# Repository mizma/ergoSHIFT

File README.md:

ergoSHIFT arcade controller
========================================================================

_**Low profile 11 button leverless arcade controller with Acrylic shell**_

This repository contains Acrylic cut design files, PCB design files and code needed to make
an arcade controller that look like this:

Also, you can create custom artwork using the stencil provided in each hardware revision folder.

(*) Above sample Artwork based on an In-Game Screenshot + Official Fan-kit (©Cygames & ARK SYSTEM WORKS)

This controller is designed with the following concept:

* Create a reasonably compact and thin leverless arcade controller
* Layout 11 main buttons + 4 directional buttons to work with the latest
  Capcom Pro-Tour rule-set
* Shift the home position for the main button one column to the right to better utilize the
  more dextrous thumb and index finger instead of the little finger.
* Add the three additionally allowed buttons
* Make the button size compatible with Snackbox MICRO from [Junkfood Arcades](https://junkfoodarcades.com/)
    * I could not find good Injection molded options other than this one.
* Make the design reversible for southpaw use.
    * To assemble for left hand use, implement all buttons on the other side.
    * Controller Circuit (Pro Micro or RP2040) must be implemented on the same side
    * to compensate for the Controller Cicuitry being implemented in reverse, Acrylic layers will need to be
      stacked in a different order and thickness.  Refer to each revision README for details

Resulting button mappings will look like this:

There are currently two revisions of the ergoSHIFT.  It uses Kailh low profile (choc v1)
mechanical keyboard switches.  The table below lists their main features.
See the README for each version for details on how to make them.

version                                 | [rev1](./hardware-rev1/)            | [rev2](./hardware-rev2/)              | [rgb](./hardware-rgb/)                |
--------------------------------------- | ----------------------------------- | ------------------------------------- | ------------------------------------- |
Status                                  | Verified                            | Verified                              | Verified                              |
case dimensions                         | 233.17x147.67x14.6mm (excl. feet)   | 233.17x147.67x14.6mm (excl. feet)     | 233.17x147.67x14.6mm (excl. feet)     |
compatibility (using provided firmware) | PC, PS3, Xinput, Switch             | PC, PS3, PS4*, PS5*, Xinput, Switch   | PC, PS3, PS4*, PS5*, Xinput, Switch   |
add-on board                            | Sparkfun Qwiic Pro Micro            | SSD1306, SH1106 or SH1107 128x64 oled | SSD1306, SH1106 or SH1107 128x64 oled |
onboard chip                            | -                                   | RP2040                                | RP2040                                |
port                                    | USB-C                               | USB-C                                 | USB-C                                 |
SMT assembly required                   | no                                  | yes                                   | yes                                   |
OLED Support                            | no                                  | yes                                   | yes                                   |
RGB Support                             | no                                  | no                                    | yes                                   |
South-paw support                       | yes                                 | yes                                   | no                                    |
firmware                                | [ATmega32U4](firmwares_atmega32u4)  | [GP2040-CE](https://gp2040-ce.info/)**| [GP2040-CE](https://gp2040-ce.info/)**|

*) for details, see the documentation in the [GP2040-CE Console Compatibility FAQ](https://gp2040-ce.info/faq/faq-console-compatibility/)

**) See [GP2040 firmware page](./firmware_GP2040-CE/) for firmware with ergoSHIFT specific config.

LICENSE
------------------------------------------------------------------------

ergoSHIFT (c) by mizma

ergoSHIFT is licensed under a
Creative Commons Attribution-ShareAlike 4.0 International License.

You should have received a copy of the license along with this
work. If not, see <https://creativecommons.org/licenses/by-sa/4.0/>.

Some portions of the work uses derivative works of other libraries and or implementations.
Firmware and hardware designs are separately licensed depending on the licensing terms of
the works it uses.  Refer to the LICENSE files or README for the relevant terms for each
component.

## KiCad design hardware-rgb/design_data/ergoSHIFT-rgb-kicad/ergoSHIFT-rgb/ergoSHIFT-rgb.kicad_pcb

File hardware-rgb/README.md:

ergoSHIFT rev RGB
========================================================================

This is a RGB rev of the ergoSHIFT.  In this version, RGB LEDs were added to each Kailh button and can be assembled onto the board by JLCPCB (or another fab house), similar to the other SMT parts. 

The firmware from the [Original GP2040-CE website](https://gp2040-ce.info/downloads) will work along with enabling the RGB LED via the GP2040-CE Web Configurator.
You may also use the firmware in the [Firmware Directory](../firmware_GP2040-CE/) which support original OLED display layout.

This version of Ergoshift has been modified to only work in the standard (non Southpaw) configuration so that there is PCB area for RGB LEDs. The Kailh sockets are also required for this version (rev2 can use Kailh sockets or switches directly) and can only be installed in the normal configuration.

All other assembly steps are the same as the hardware-rev2 steps

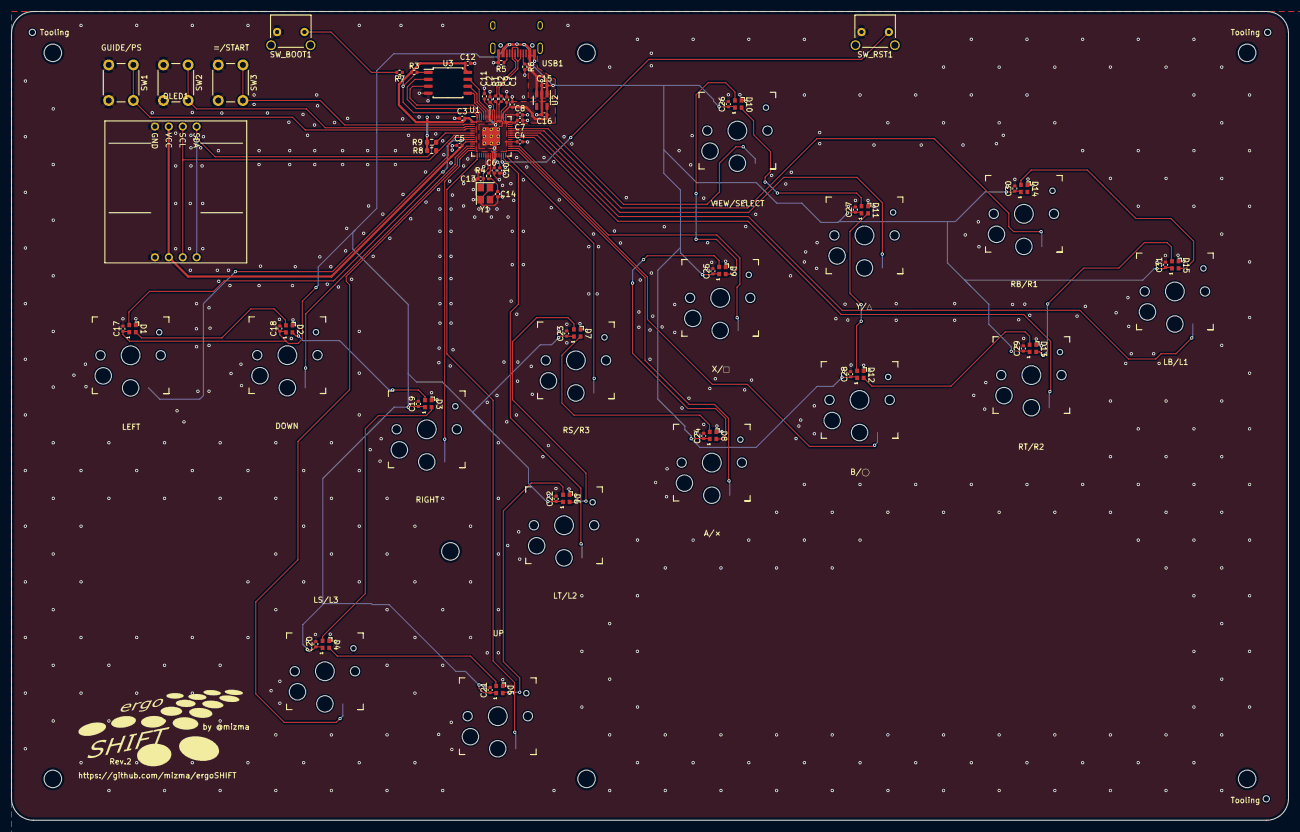
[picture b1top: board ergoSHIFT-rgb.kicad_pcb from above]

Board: 2 copper layers, 233.2 x 147.7 mm, 84 parts (0 on the bottom side), 56 nets.

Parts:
C1, C9, C15, C16: 1u; C_0402_1005Metric
C2, C3, C4, C5, C6, C7, C8, C10, C11, C12: 100n; C_0402_1005Metric
C13, C14: 30p; C_0402_1005Metric
C17, C18, C19, C20, C21, C22, C23, C24, C25, C26, C27, C28, C29, C30, C31: 100nF; C_0402_1005Metric
D1, D2, D3, D4, D5, D6, D7, D8, D9, D10, D11, D12, D13, D14, D15: SK6812-EC20; LED_SK6812_EC20_2.0x2.0mm
OLED1: OLED_DISP_0.96inch_Reversible
R1, R2: 27; R_0402_1005Metric
R3: 10k; R_0402_1005Metric
R4, R7: 1k; R_0402_1005Metric
R5, R6: 5.1k; R_0402_1005Metric
R8, R9: 4.7k; R_0603_1608Metric
SW1, SW2, SW3: SW_Push; SW_PUSH_6mm_H8.5mm
SW4, SW5, SW6, SW7, SW8, SW9, SW10, SW11, SW12, SW13, SW14, SW15, SW16, SW17, SW18: SW_Push; Kailh_socket_PG1350
SW_BOOT1: SW_PUSH; SW_Tactile_Yushakobo 3x6x4.3mm
SW_RST1: SW_PUSH; SW_Tactile_Yushakobo 3x6x4.3mm
Tooling: JLCPCB_Tooling
Tooling#2, Tooling#3: JLCPCB_Tooling
U1: RP2040; RP2040-QFN-56
U2: TLV73333PDBV; SOT-23-5
U3: W25Q128JVS; SOIC-8_5.23x5.23mm_P1.27mm
USB1: HRO-TYPE-C-31-M-12; HRO-TYPE-C-31-M-12-Assembly
Y1: Crystal_GND24; Crystal_SMD_3225-4Pin_3.2x2.5mm

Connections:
+1V1: C9.1, C10.1, C11.1, U1.23 (DVDD), U1.45 (VREG_VOUT), U1.50 (DVDD)
+3V3: C1.1, C2.1, C3.1, C4.1, C5.1, C6.1, C7.1, C8.1, C12.1, C16.1, OLED1.2 (VCC), R3.1, R8.1, R9.2, U1.1 (IOVDD), U1.10 (IOVDD), U1.22 (IOVDD), U1.33 (IOVDD), U1.42 (IOVDD), U1.43 (ADC_AVDD), U1.44 (VREG_IN), U1.48 (USB_VDD), U1.49 (IOVDD), U2.5 (OUT), U3.8 (VCC)
+5V: C15.1, C17.1, C18.1, C19.1, C20.1, C21.1, C22.1, C23.1, C24.1, C25.1, C26.1, C27.1, C28.1, C29.1, C30.1, C31.1, D1.1 (VDD), D2.1 (VDD), D3.1 (VDD), D4.1 (VDD), D5.1 (VDD), D6.1 (VDD), D7.1 (VDD), D8.1 (VDD), D9.1 (VDD), D10.1 (VDD), D11.1 (VDD), D12.1 (VDD), D13.1 (VDD), D14.1 (VDD), D15.1 (VDD), U2.1 (IN), U2.3 (EN), USB1.2 (VBUS), USB1.11 (VBUS)
A: SW16.1, U1.29 (GPIO18)
B: SW17.1, U1.30 (GPIO19)
DOWN: SW5.1, U1.12 (GPIO9)
GND: C1.2, C2.2, C3.2, C4.2, C5.2, C6.2, C7.2, C8.2, C9.2, C10.2, C11.2, C12.2, C13.1, C14.2, C15.2, C16.2, C17.2, C18.2, C19.2, C20.2, C21.2, C22.2, C23.2, C24.2, C25.2, C26.2, C27.2, C28.2, C29.2, C30.2, C31.2, D1.3 (GND), D2.3 (GND), D3.3 (GND), D4.3 (GND), D5.3 (GND), D6.3 (GND), D7.3 (GND), D8.3 (GND), D9.3 (GND), D10.3 (GND), D11.3 (GND), D12.3 (GND), D13.3 (GND), D14.3 (GND), D15.3 (GND), OLED1.1 (GND), R5.2, R6.2, SW1.2, SW2.2, SW3.2, SW4.2, SW5.2, SW6.2, SW7.2, SW8.2, SW9.2, SW10.2, SW11.2, SW12.2, SW13.2, SW14.2, SW15.2, SW16.2, SW17.2, SW18.2, SW_BOOT1.1, SW_RST1.1, U1.19 (TESTEN), U1.57 (GND), U2.2 (GND), U3.4 (GND), USB1.1 (GND), USB1.12 (GND), Y1.2, Y1.4
HOME: SW1.1, U1.4 (GPIO2)
L1: SW13.1, U1.36 (GPIO24)
L2: SW15.1, U1.27 (GPIO16)
L3: SW7.1, U1.13 (GPIO10)
LEFT: SW4.1, U1.8 (GPIO6)
unnamed: C14.1, R4.1, Y1.3
unnamed: R7.2, SW_BOOT1.2
unnamed: SW_RST1.2, U1.26 (RUN)
unnamed: R2.2, U1.46 (USB_DM)
unnamed: R1.2, U1.47 (USB_DP)
unnamed: R6.1, USB1.4 (CC1)
unnamed: R5.1, USB1.10 (CC2)
OLED_SCL: OLED1.3 (SCL), R8.2, U1.7 (GPIO5)
OLED_SDA: OLED1.4 (SDA), R9.1, U1.6 (GPIO4)
OPT: SW2.1, U1.3 (GPIO1)
QSPI_SCLK: U1.52 (QSPI_SCLK), U3.6 (CLK)
QSPI_SD0: U1.53 (QSPI_SD0), U3.5 (DI(IO0))
QSPI_SD1: U1.55 (QSPI_SD1), U3.2 (DO(IO1))
QSPI_SD2: U1.54 (QSPI_SD2), U3.3 (IO2)
QSPI_SD3: U1.51 (QSPI_SD3), U3.7 (IO3)
QSPI_SS: R3.2, R7.1, U1.56 (QSPI_SS), U3.1 (~CS)
R1: SW12.1, U1.38 (GPIO26_ADC0)
R2: SW18.1, U1.35 (GPIO23)
R3: SW9.1, U1.28 (GPIO17)
RGB_DATA_A: D7.2 (DOUT), D8.4 (DIN)
RGB_DATA_B: D11.2 (DOUT), D12.4 (DIN)
RGB_DATA_DOWN: D1.2 (DOUT), D2.4 (DIN)
RGB_DATA_LB: D14.4 (DIN), D15.2 (DOUT)
RGB_DATA_LEFT: D1.4 (DIN), U1.9 (GPIO7)
RGB_DATA_LS: D3.2 (DOUT), D4.4 (DIN)
RGB_DATA_LT: D5.2 (DOUT), D6.4 (DIN)
RGB_DATA_RB: D13.2 (DOUT), D15.4 (DIN)
RGB_DATA_RIGHT: D2.2 (DOUT), D3.4 (DIN)
RGB_DATA_RS: D6.2 (DOUT), D7.4 (DIN)
RGB_DATA_RT: D12.2 (DOUT), D13.4 (DIN)
RGB_DATA_SEL: D9.2 (DOUT), D10.4 (DIN)
RGB_DATA_UP: D4.2 (DOUT), D5.4 (DIN)
RGB_DATA_X: D8.2 (DOUT), D9.4 (DIN)
RGB_DATA_Y: D10.2 (DOUT), D11.4 (DIN)
RIGHT: SW6.1, U1.14 (GPIO11)
SEL: SW14.1, U1.39 (GPIO27_ADC1)
START: SW3.1, U1.2 (GPIO0)
UP: SW8.1, U1.15 (GPIO12)
USB_DM: R2.1, USB1.5 (DN2), USB1.7 (DN1)
USB_DP: R1.1, USB1.6 (DP1), USB1.8 (DP2)
X: SW10.1, U1.31 (GPIO20)
XIN: C13.2, U1.20 (XIN), Y1.1
XOUT: R4.2, U1.21 (XOUT)
Y: SW11.1, U1.37 (GPIO25)

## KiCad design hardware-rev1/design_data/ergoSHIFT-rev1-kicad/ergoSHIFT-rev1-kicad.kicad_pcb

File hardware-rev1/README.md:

ergoSHIFT rev1
========================================================================

This is rev1 of the ergoSHIFT.  In this version an Arduino Pro Micro
is soldered onto the main PCB.

To make one you will need:

* [acrylic shell](./acrylic-shell/)
    * For Standard Layout
        * Layers 1, 2, 4: 3mm
        * Layers 3, 5: 2mm
    * For Reverse Layout (Left handed)
        * Layers 1, 2, 3: 3mm
        * Layers 4, 5: 2mm
* [the ergoSHIFT PCB](./pcb/)
* Arduino Pro Micro [SparkFun Qwiic Pro Micro - USB-C (ATmega32U4)](https://www.sparkfun.com/products/15795)
* 15x Kailh low profile (choc v1) switches of your choice
    * I use Kailh Choc v1 Red Pro (Linear and low activation force: 35±10gf with actuation travel: 1.5±0.5mm)
    * Light Blue (gChoc) can be used for even lower actuation force.
* (optionally) 15x Kailh low profile hotswap sockets
* Button Caps (Choose one)
    * [MICRO keycap set](https://junkfoodarcades.com/collections/micro-accessories)
        * You will need to buy two sets of Snackbox Micro keycap sets.
    * [3D printed buttoncaps](../3d-printed-buttoncaps)
* 3x 6x6x8.51mm tact switches
    * I Used [TE Connectivity 3-1825910-5](https://www.te.com/ja/product-3-1825910-5.html)
* 1x 3x6x4.3 horizontal tact switch
    * https://www.newegg.com/p/2S7-01KR-035X0
    * https://shop.yushakobo.jp/collections/all-keyboard-parts/products/a1600ed-01-1
    * [schematics](images/tactile-switch_3x6x4.3.jpg)
* 7x M3 screws (length 20mm)
    * Acryl top 2mm * 2 + 3mm = 7mm
    * PCB 1.6mm
    * Acryl bottom 3mm * 2 = 6mm
    * Rubber feet screw depth = 3mm (using rubber feet below.  adjust for your part)
    * Rubber feet total depth = 8mm (using rubber feet below.  adjust for your part)
    * M3 nut height = 2mm
    * min length = 19.6mm (using rubber feet below.  adjust for your part)
    * max length = 22.6mm (using rubber feet below.  adjust for your part)
* 7x M3 nut and acompanying rubber feet
    * Rubber feet Tochigiya [TM-TK-15](https://www.monotaro.com/p/0933/2486/?displayId=5)
    * The position of the holes are intended for feet radius of less than 8mm
* Some Tin coated wires
* a soldering iron
    * something with enough power is better 
      (i.e. [Hakko FX 600](https://www.hakko.com/japan/products/hakko_fx600_set.html))
    * I recommend changing tips to D type for most Through-hole soldering, or C type if you plan to
      solder SMT as well. (default B tips are harder to use for most PCB soldering)
    * Use 320C ~ 370C temp recommended (can be changed if you know your way around)

## Assembly Instructions

### Ordering PCB

I used [JLCPCB](https://jlcpcb.com/).  Just upload the gerber files in [pcb](pcb) and keep most parameters default.
You may change PCB Qty and PCB Color if you like.  All other parameters should be kept the same.

### Ordering Buttons

#### Snackbox Micro button caps

ergoSHIFT is compatible with Snackbox Micro button caps.

You can purchase them [HERE](https://junkfoodarcades.com/collections/micro-accessories)

#### 3D printed buttons

_**Currently verifying design**_

If you have a 3D printer, print at your own will.  Files are found [here](../3d-printed-buttoncaps/).

* [ergoSHIFT-ButtonCapBig.stl](../3d-printed-buttoncaps/ergoSHIFT-ButtonCapBig.stl) 
  is used for the thumb button. 1 board needs 1 of this button.
* [ergoSHIFT-Buttoncap.stl](../3d-printed-buttoncaps/ergoSHIFT-ButtonCapBig.stl) is used for all other buttons.
  1 board needs 14 of this button.
* [ergoSHIFT-FullSetButtonCaps.stl](../3d-printed-buttoncaps/ergoSHIFT-FullSetButtonCaps.stl) is an STL file 
  containing 1 full set of buttons + extra(26 small and 2 big.).  If your 3D printing service allows 28 or more shells, it may be cheaper to print in one batch using this STL file.
    * Print size needs to be bigger than X：99.4901mm x Y： 91.7951mm x Z： 15.0000mm
    * To accomodate for the buttons in the 100mm x 100mm x 100mm size limit in some Printing services,
      This STL file has two layers of buttons arranged on top of each other.  This type of layout is only
      possible on print technology such as SLS or MJF.  Check with your 3D Printing service.
    * If your 3D Printing service does not support this type of data, use individual cap data to print.

Insertion portion may need to be adjusted in size for your 3D Printer and settings to fit snugly to the switch.
You may use some of the printer features but if that doesn't work, you might want to edit the original model.
Model data are found in [here](../3d-printed-buttoncaps/design_data/) in a [FreeCAD](https://www.freecadweb.org/)
file format.

Also, since the insertion portion requires a fairly tight tolerance which is not easily achieved by 3D printers,
the models are modelled slightly on the larger side.

I have had fairly good results with this model using SLS/MJF Nylon print but sometimes it is too large.
If the legs turn out too large to fit, use sandpaper to adjust the width of the legs.

#### Materials Consideration

* Nylon
    * May be a good place to start for tensile strength and good chemical stability.
    * can be pretty strong if printed using SLS process at some printing services
    * may be prone to warping.  not good for humid places.
* UV Resin
    * Also pretty strong as a material, and stronger to humidity.
    * Maybe slightly more brittle than Nylon

### Ordering Acrylic cuts

I use [Elecrow](https://www.elecrow.com/acrylic-cutting.html) to cut acrylic.

Upload the .zip file in [acrylic-shell](acrylic-shell/) to the Elecrow Acrylic cut service to order.
.Zip file includes the dxf file and the dimentions.txt file.  PDF is just for reference.

Use the following thickness:

* For Standard Layout
    * Layers 1, 2, 4: 3mm
    * Layers 3, 5: 2mm
* For Reverse Layout (Left handed)
    * Layers 1, 2, 3: 3mm
    * Layers 4, 5: 2mm

The original design file (FreeCAD file) can be found [here](./design_data/acryl-design/).

The Acrylic should look like the following (with PCB stacked)

(*) Above image is for standard layout (right handed)

### Assembly

1. Solder all the Choc v1 switches and the tactile switches.  make sure you populate the side with the logo.
    * If you populate the side with the logo on the left, the parts only goes in in the correct orientation.
        * For reverse layout, implement the buttons on the other side as shown in [this picture](images/Reverse-Layout-Solering.jpg)
    * If you use the hot-swap sockets, those will go on the back. (see silk screen on back side for orientation)
        * For hotswap sockets, pre-solder one side of the pad on PCB, place the socket, heat the pre-solder while
          pressing down on the socket to attach the socket.  After It is attached, solder the other side fully and then add more solder on the pre-soldered side.
2. Solder the Pro Micro Qwiic from the bottom side of the PCB up into the slit (USB socket should be between the cut-outs on the board, facing up) (Following instruction is how I did it.  There may be other ways) (This should NOT BE REVERSED for left hand layout)
    1.  First, mask the back side holes on the PCB with masking tape, and poke a small hole in each Through-hole with a needle. (This is to stop creating solder filets on the side the ProMicro will be soldered to.
        
    2. Insert a short (2~3cm) tin coated wire in the hole and solder onto the board.  Then cut the excess wire on the front side.

    3. Remove the masking tape.  The back side should have a flat solder filled hole with wires coming out the middle.
       
    4. Place the Pro-Micro into the wires, tape it down to place.  Also tape the entire front side of 
       the soldered through-holes so the wires don't fall when solder melts.
       
    5. Solder the Pro-Micro to the tin-coated wire.
       
3. stack the Acryl and PCB in following order: Layer 01, Layer 02, PCB, Layer 03, Layer 04 and Layer 05.
    * If you use 2 Layer 4s, the order should be 01, 02, 03, 04, 04.
4. Screw on the M3 screws with the nut on all 7 locations.  Rubber feet should be inserted at least in the 4 corners between the nut and the acrylic.

It should look like the following when assembled.

### Pro-Tip 1. Filing the Acrylic Edges

Acrylic Edges after laser cutting can be quite sharp and do not feel good.
You may want to file the edges with sandpaper (#400 is a nice place to start) to remove the edges 
on the top acrylic layer so it does not feel bad.

### Pro-Tip 2. Customizing design

You can also insert some artwork below the top acrylic layer as below:

(*) Above sample Artwork based on an In-Game Screenshot + Official Fan-kit (©Cygames & ARK SYSTEM WORKS)

Stencil for the artwork can be found below (Page size set to A4):

* [Stencil SVG](./images/ergoSHIFT-stencil.svg)
* [Stencil PNG 300dpi](./images/ergoSHIFT-stencil.png)
* [Southpaw Stencil SVG](./images/ergoSHIFT-stencil-reverse.svg)
* [Southpaw Stencil PNG 300dpi](./images/ergoSHIFT-stencil-reverse.png)

To cut the stencil, use one of the top acrylic plates as cutting guides (don't trust the acuracy
of the printed stencil mark, they are good enough to use as design guide, but not acurate enough for 
final cutting guide).  It is easy to cut if you tape the plate on top of the print and use a sharp
designers knife.

## License and Acknowlegements

PCB design licensed under [CC BY-SA 4.0](https://creativecommons.org/licenses/by-sa/4.0/) by mizma

Acrylic sandwitching shell heavily inspired by [Mille-Feuille](https://pomegd.booth.pm/items/2685530) 
by [@pomegd](https://twitter.com/pomegd)

PCB design uses the following libraries or derivatives of the design:

* [keyswitches.pretty](https://github.com/daprice/keyswitches.pretty) by [daprice](https://github.com/daprice) ([CC BY-SA 4.0](https://creativecommons.org/licenses/by-sa/4.0/))
* [ProMicroKiCad](https://github.com/Biacco42/ProMicroKiCad) by [Biacco42](https://github.com/Biacco42), derived from [teensy\_library](https://github.com/XenGi/teensy_library) by Ricardo Band ([MIT License](https://opensource.org/licenses/mit-license.php))

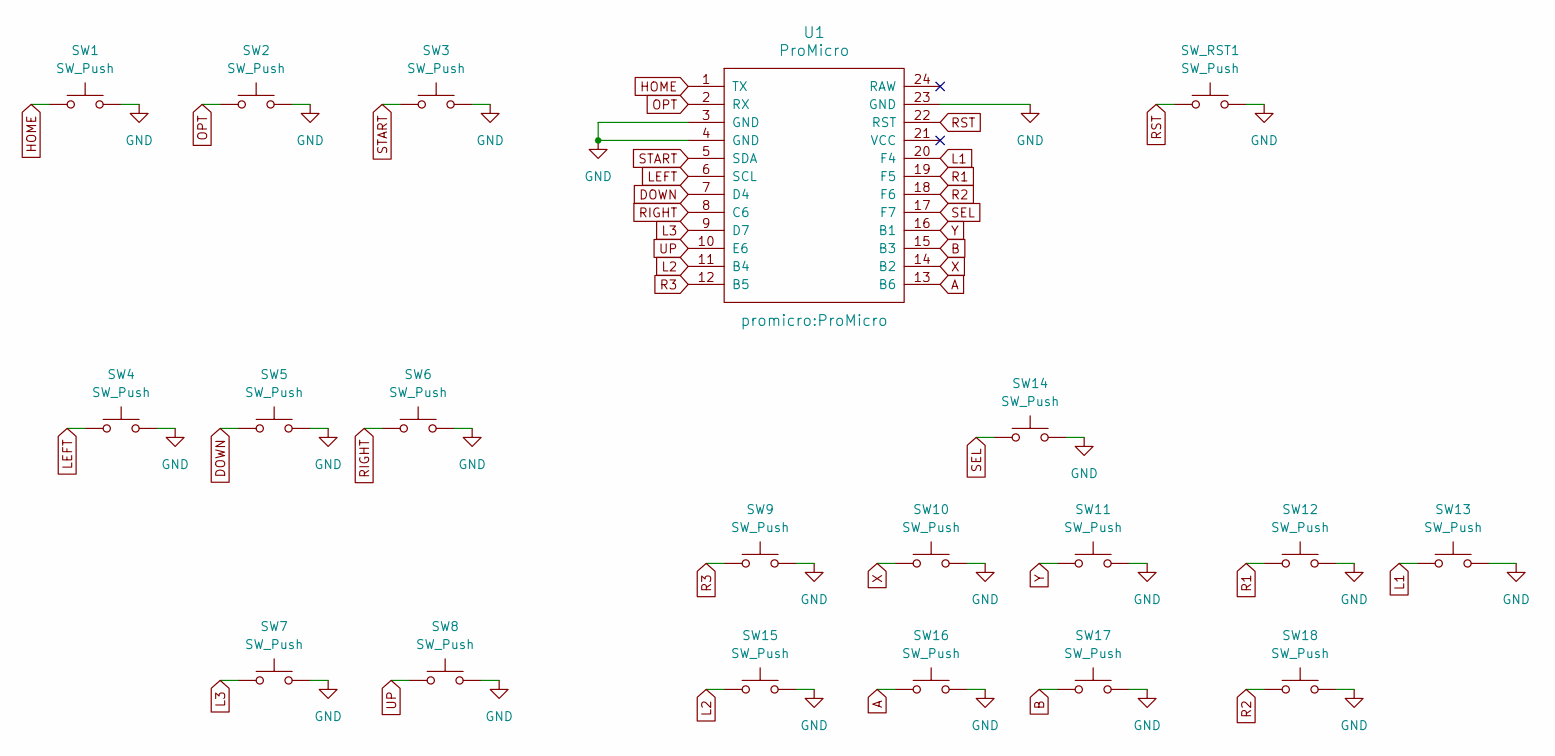
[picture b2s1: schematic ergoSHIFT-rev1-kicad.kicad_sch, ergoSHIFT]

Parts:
SW1, SW2, SW3: SW_Push; SW_PUSH_6mm_H8.5mm
SW4, SW5, SW6, SW7, SW8, SW9, SW10, SW11, SW12, SW13, SW14, SW15, SW16, SW17, SW18: SW_Push; Kailh_socket_MX_optional
SW_RST1: SW_Push; SW_Tactile_Yushakobo 3x6x4.3mm
U1: ProMicro

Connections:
A: SW16.1, U1.13 (B6)
B: SW17.1, U1.15 (B3)
DOWN: SW5.1, U1.7 (D4)
GND: SW1.2, SW2.2, SW3.2, SW4.2, SW5.2, SW6.2, SW7.2, SW8.2, SW9.2, SW10.2, SW11.2, SW12.2, SW13.2, SW14.2, SW15.2, SW16.2, SW17.2, SW18.2, SW_RST1.2, U1.3 (GND), U1.4 (GND), U1.23 (GND)
HOME: SW1.1, U1.1 (TX)
L1: SW13.1, U1.20 (F4)
L2: SW15.1, U1.11 (B4)
L3: SW7.1, U1.9 (D7)
LEFT: SW4.1, U1.6 (SCL)
OPT: SW2.1, U1.2 (RX)
R1: SW12.1, U1.19 (F5)
R2: SW18.1, U1.18 (F6)
R3: SW9.1, U1.12 (B5)
RIGHT: SW6.1, U1.8 (C6)
RST: SW_RST1.1, U1.22 (RST)
SEL: SW14.1, U1.17 (F7)
START: SW3.1, U1.5 (SDA)
UP: SW8.1, U1.10 (E6)
X: SW10.1, U1.14 (B2)
Y: SW11.1, U1.16 (B1)

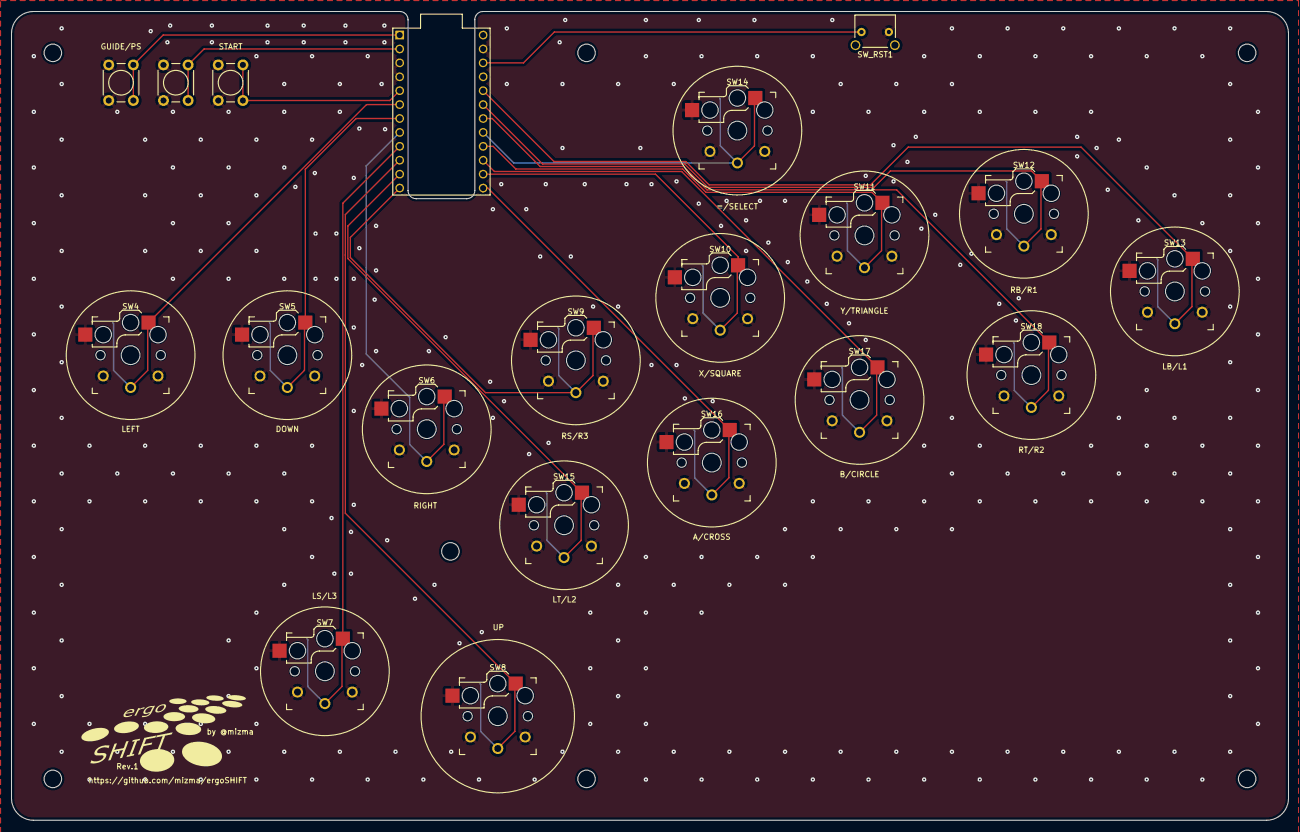
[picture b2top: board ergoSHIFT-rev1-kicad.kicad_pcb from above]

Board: 2 copper layers, 233.2 x 147.7 mm, 20 parts (0 on the bottom side), 20 nets.

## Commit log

2023-12-15 Initial commit with Acryl design data and button layout design sketch
2023-12-16 acryl stackup data upload
2023-12-16 package acryl cut data for sending to Elecrow. Added design stencil image
2023-12-16 move image to hardware revision specific folder
2023-12-16 initial design complete for Acryl and PCB
2023-12-16 ignore backups
2023-12-16 Add Readme for Top directory. add Firmware files (button mappings not fixed)
2023-12-16 Added README for rev1 hardware directory.
2023-12-16 add switch schematics
2023-12-16 added referenced footprint library
2023-12-16 fixed issue with PCB coordinate origin settings. fixed stencil being too light.
2023-12-20 Fix stencil icons for view and menu button for xbox style button icons
2023-12-20 add future rev.2 plan
2023-12-20 ignore build folder
2023-12-20 Fix firmware pin assign for ergoSHIFT circuit design
2023-12-20 Fix readme for the firmwares.
2023-12-20 fix Readme
2023-12-20 Switch Licenses.
2023-12-20 add oled splash size logo image and c header binary version
2023-12-20 fix some image issues.
2023-12-23 add initial implementation for rev2
2023-12-23 add readme for rev.2
2023-12-24 updated stencil with logo. added circuit schematics for rev2
2023-12-24 Finalize design of rev.1 and fix README.
2023-12-24 Fix minor missing point in Readme
2023-12-24 Added southpaw version of the stencils
2023-12-24 Add description in Firmware readme for how to build for Southpaw pinout.
2023-12-24 Update README.md
    typo!
2023-12-25 Update README.md
    add custom art variation image
2023-12-29 update image
2024-01-05 update stencil and add backplate stencil plus shortcut cheat-sheet
2024-01-05 update Readme for rev2 hardware.
2024-01-05 Update top README file and added necessary Firmware Files for the time being.
2024-01-05 Fix documentation.
2024-01-05 Fix setting issues.
2024-01-06 Update README.md
    removing temporary "Not Verified" note
2024-01-06 Update README.md
    Update thickness of Acrylic layer 1
2024-01-06 Fix Acrylic layer 1 thickness designation on data files
2024-01-06 Initial design upload for 3D Printable Caps
2024-01-06 Updated documents for Rev2 build instructions and a few firmware related descriptions.
    Fix config file default pin mapping
2024-01-08 Cleanup technical drawing for acrylic layer and pcb
2024-01-08 update elecrow upload files with new tech drawing
2024-01-08 remove unnecessary dimention on layer 02 drawing
2024-01-10 update firmware build to 0.7.7-RC1
2024-01-12 Update PCBA instruction
2024-01-13 update button cap design.
    * adjust leg size. too large for MJF PA12W print.
    * adjust diameter of main buttons for better clearance
    * adjest wall height of main buttons to avoid conflict with switch assy
2024-01-19 update pre-built binary to 0.7.7 and update config related files for pin mapping to the 0.7.7 format.
2024-01-19 3D button caps now confirmed to work
2024-01-28 add image and readme to 3d printed caps + southpaw build
2024-02-03 typo fix
2024-02-04 update button cap leg size.
    button cap legs seems to get larger on MJF prints. setting the legs to be almost equal size with the kailh choc v1 switch drawing dimensions
2024-04-17 update to v0.7.8 firmware.
2024-05-18 update documentation for OLED soldering instruction to avoid issues.
2024-05-19 added custom display layout
2024-05-19 correctly configured environment before building firmware
2024-05-20 adding memo to point to the current pre-built firmware sourcecode.
2024-05-26 update README to include optional firmware builds
2024-05-26 fix typo
2024-06-05 Add link to the repo hosting latest firmware
2024-06-08 update firmware instructions
2024-09-09 added RGB LED design
2024-09-09 removed cost info, unnecessary
2024-09-10 added images and README file
2024-09-10 rotated image
2024-09-10 removing image
2024-09-10 restoring image
2024-09-11 added .DS_Store to gitignore and removed bottom placement file (unneeded)
2024-09-11 removed .DS_Store properly
2024-09-11 removed extra gerber where I added a personal logo and updated silkscreen in the design to remove
2024-09-11 last update to kicad design files to bring them to current status
2024-09-15 removed extra Kicad backup files, updated PCB files to remove extraneous bottom side silkscreen, updated README to reflect this information
2024-09-15 updated README and gerbers, removed bottom side silk
2024-09-15 updated README, removed extraneous bottom silk, updated gerber
2024-09-15 removed the backup files for real
2024-09-15 removed extra *.kicad_sch_old.kicad_sch file
2024-09-15 RGB LED Revision (#13)
    * added RGB LED design
    * removed cost info, unnecessary
    * added images and README file
    * Update README.md
    * rotated image
    * removing image
2024-10-05 update firmware related information in README
2024-10-05 fix outdated info
2024-10-07 switched R1/L1 to reflect correct LED order
2024-10-07 Update README.md
    added ? to image url to force image update
2024-10-07 Updated LED config image to set proper order for LEDs (#16)
    * switched R1/L1 to reflect correct LED order
    * Update README.md
    added ? to image url to force image update
    ---------
2025-09-05 update firmware information

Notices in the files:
hardware-rev1/README.md:
License and Acknowlegements:
PCB design licensed under [CC BY-SA 4.0](https://creativecommons.org/licenses/by-sa/4.0/) by mizma
Acrylic sandwitching shell heavily inspired by [Mille-Feuille](https://pomegd.booth.pm/items/2685530)
by [@pomegd](https://twitter.com/pomegd)
PCB design uses the following libraries or derivatives of the design:
[keyswitches.pretty](https://github.com/daprice/keyswitches.pretty) by [daprice](htt
